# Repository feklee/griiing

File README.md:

The idea for the GIIIRNG is that it’s a ring light on a PCB that
screws into the ring mount of the Ricoh GRⅢ.

For an experimental LED flash tested with the GRⅢ, see my repo
[led-flash][1].

License
=======

Except where noted otherwise, files are licensed under the WTFPL.

Copyright © 2020 [Felix E. Klee](felix.klee@inka.de)

This work is free. You can redistribute it and/or modify it under the terms of
the Do What The Fuck You Want To Public License, Version 2, as published by Sam
Hocevar. See the COPYING file for more details.

[1]: https://github.com/feklee/led-flash

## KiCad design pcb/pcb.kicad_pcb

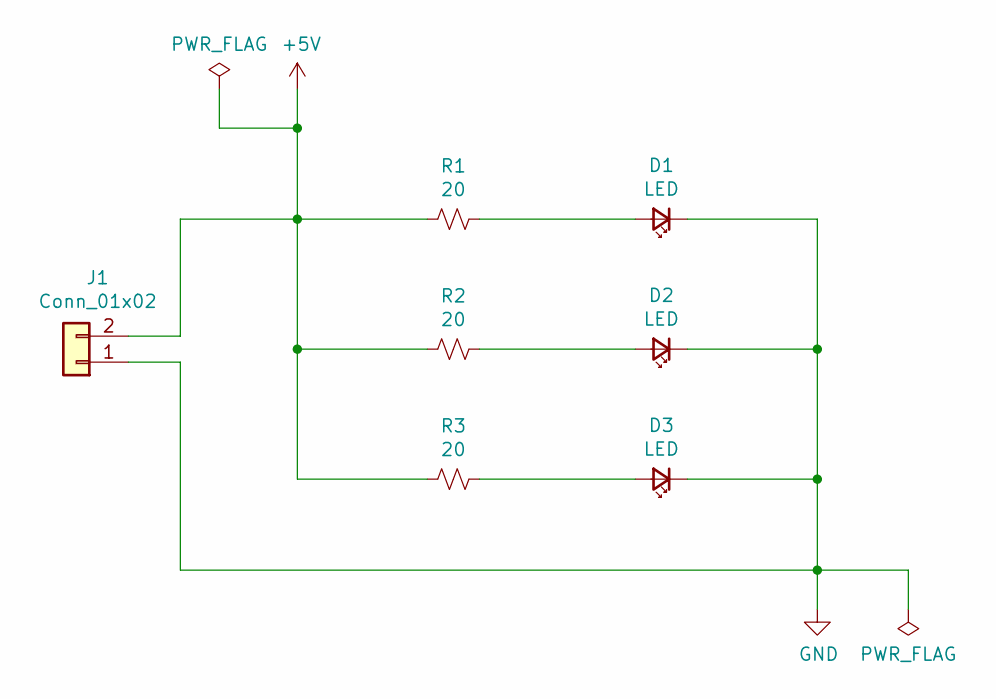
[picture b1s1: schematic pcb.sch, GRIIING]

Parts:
D1, D2, D3: LED; Universal_LED
J1: Conn_01x02; Power_Connection
R1, R2, R3: 20; R_0805_2012Metric_Pad1.20x1.40mm_HandSolder

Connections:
+5V: J1.2, R1.1, R2.2, R3.2
GND: D1.1 (K), D2.1 (K), D3.1 (K), J1.1
unnamed: D1.2 (A), R1.2
unnamed: D2.2 (A), R2.1
unnamed: D3.2 (A), R3.1

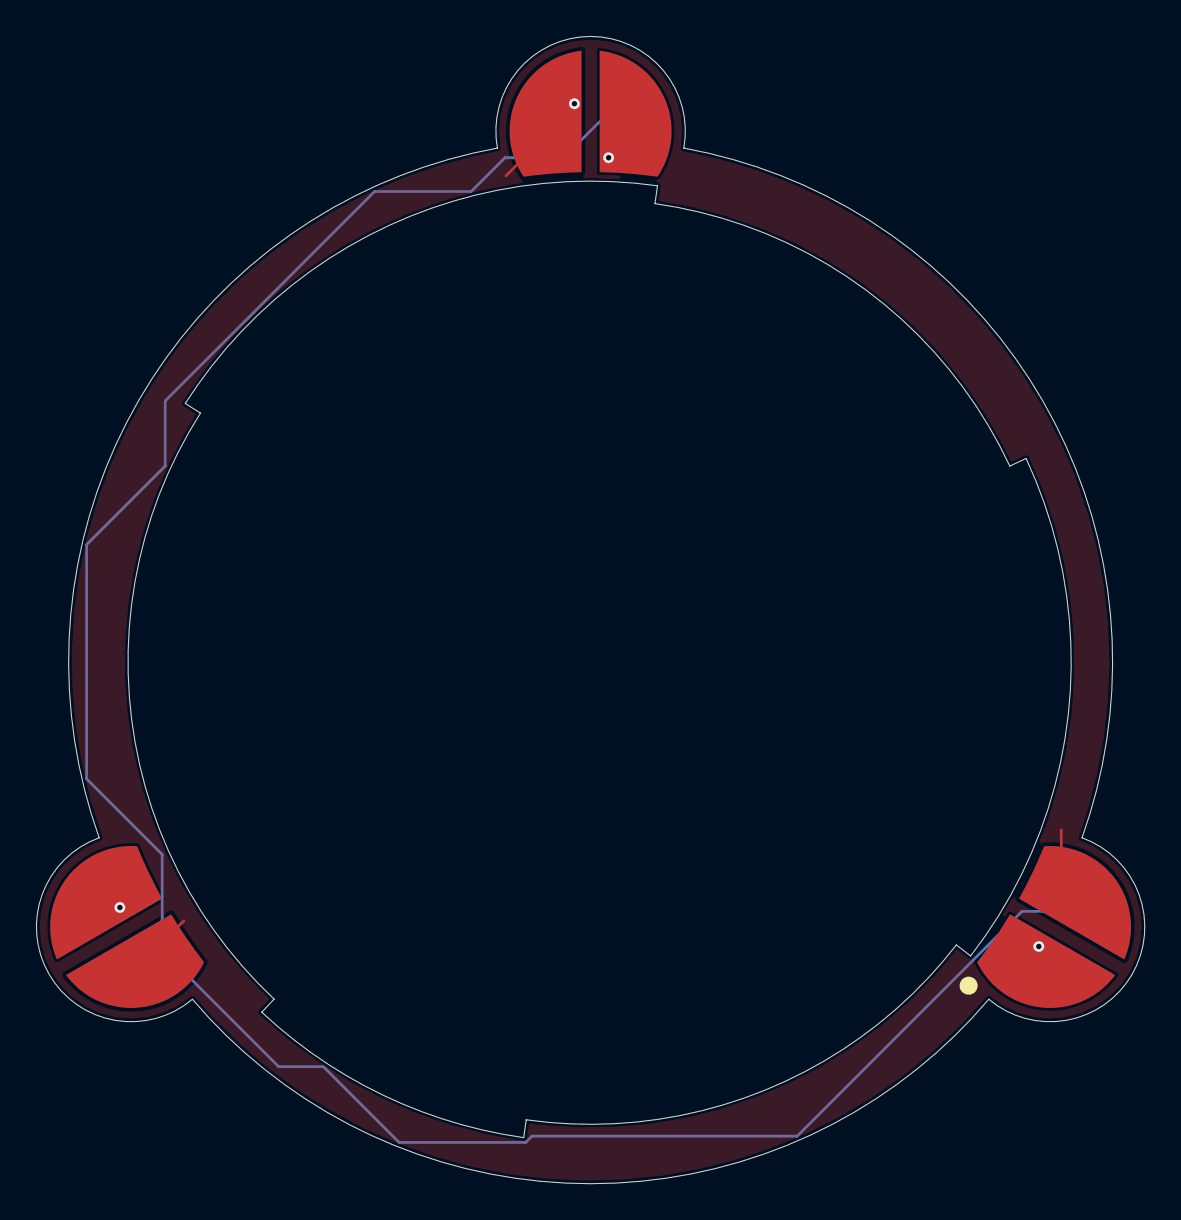
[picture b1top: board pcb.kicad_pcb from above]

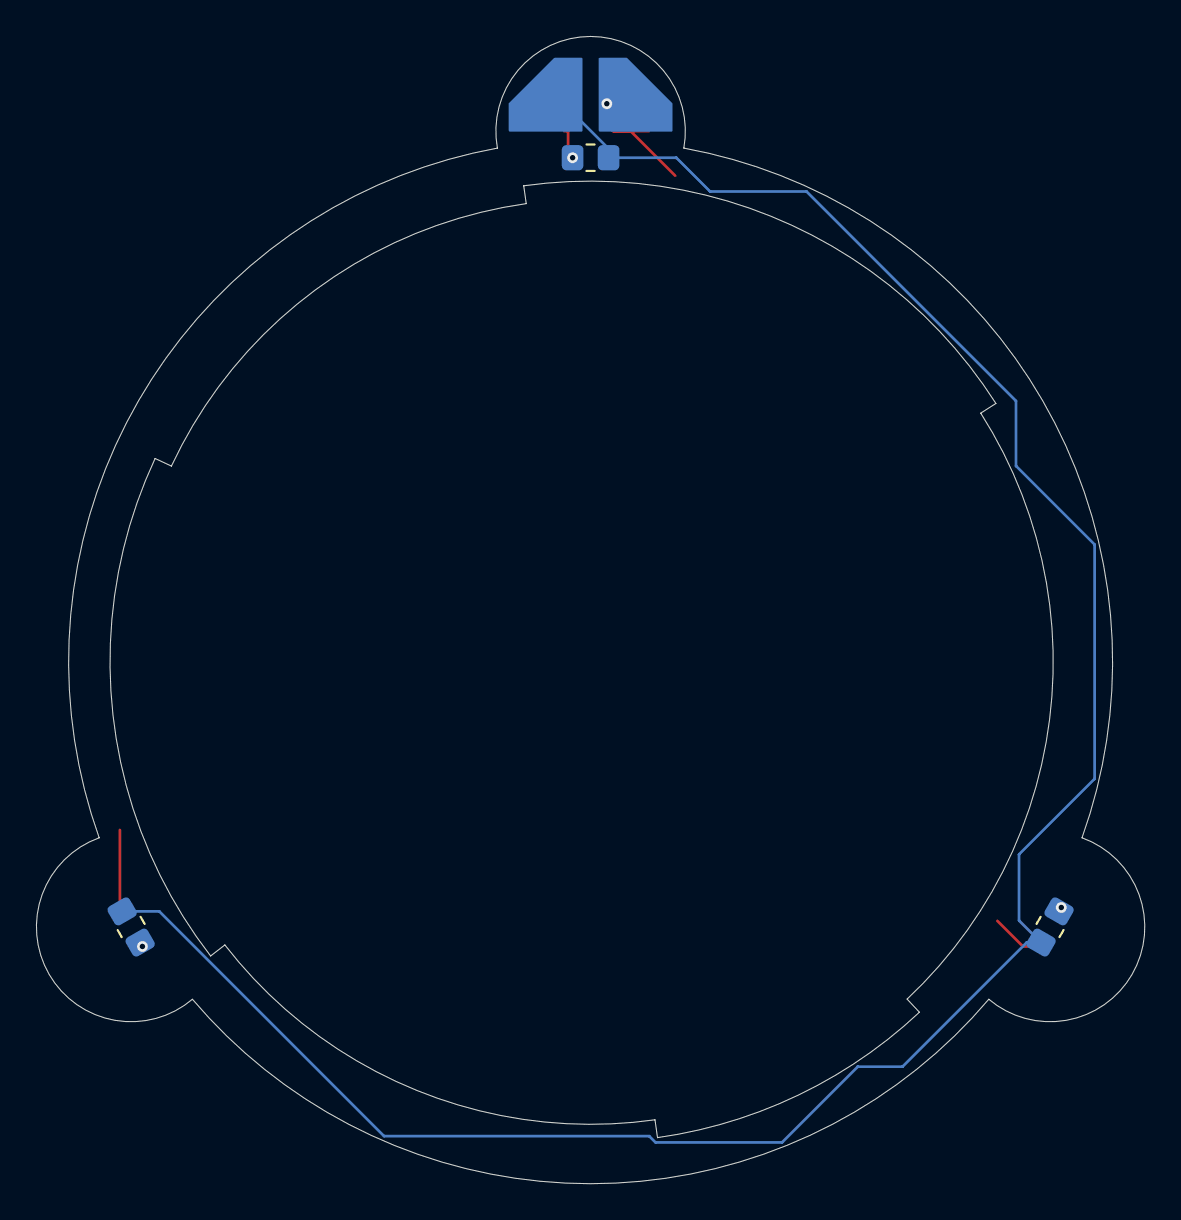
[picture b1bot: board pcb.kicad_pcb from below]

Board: 2 copper layers, 61.6 x 63.7 mm, 7 parts (4 on the bottom side), 5 nets.

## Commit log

2020-11-16 Explain
2020-11-16 Ignore Rhino3D cache, backup, and lock files
2020-11-16 Add sketch with outline for KiCad
2020-11-16 Add KiCad project for electronics
2020-11-16 Ignore certain KiCad files
2020-11-16 Add basic schematic
2020-11-16 Assign footprints
2020-11-17 Create custom LED footprint for flexible sizes
2020-11-17 Add power flags
2020-11-17 Create basic board layout (incomplete)
2020-11-17 Add positions for components
2020-11-17 Go back to custom LED footprint (from testing one)
2020-11-17 Reroute, repour
2020-11-17 Update capitalization
2020-11-17 Create easier to solder power connection
2020-11-17 Use new power connection
2020-11-17 Add more space between LED pads
2020-11-17 Add more space between pads
2020-11-17 Fix numbering
2020-11-17 Update LED footprints
2020-11-17 Add alignment point on silkscreen
2020-11-17 Adjust export settings for Gerbers
2020-11-18 Add rendering of board
